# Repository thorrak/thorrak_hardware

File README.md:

# Thorrak's Hardware Designs
This repo is a collection of PCBs and other hardware designs I've made for various projects I've released. More information can be found on pages for each of the projects themselves.

**Note** - While the majority of the hardware for my projects is contained in this repo, the software is broken out into individual projects on GitHub. Most firmware can be flashed using [BrewFlasher](http://www.brewflasher.com/).

## BrewPi-ESP

The BrewPi-ESP project reimplements the BrewPi firmware on an ESP8266, ESP32, and ESP32-S2. 

- [Hardware Designs](BrewPi-ESP.md)
- [Project on GitHub](https://github.com/thorrak/brewpi-esp8266)

## TiltBridge

The TiltBridge project provides a Bluetooth-to-WiFi bridge for Tilt Hydrometers

- [Hardware/Container Designs](TiltBridge.md)
- [Project on GitHub](https://github.com/thorrak/tiltbridge/)

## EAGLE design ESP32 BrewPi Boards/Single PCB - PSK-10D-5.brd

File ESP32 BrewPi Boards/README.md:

# ESP32 BrewPi Controller Boards

# NOTE - This document is NOT complete/verified yet. 
## Please do not base a build on this doc without consulting Thorrak directly first!

Although the "heart" of a BrewPi controller is the microprocessor running the BrewPi-compatible firmware, without other
connected components that microcontroller cannot sense temperature, control power, or do any of the other things that
make a temperature controller useful. For the ESP32 version of this project, I have designed a single, "one size fits 
most" PCB that should work for virtually all builds -- as well as a handful of true "all-in-one" PCBs which integrate
the 5V 2A AC-to-DC power supply and 2-channel relay board that are typically required to be purchased/integrated
separately. 

| Board Design                                                                 | Tindie Order Link                                                                 | OSHPark Order Link                                    |
|------------------------------------------------------------------------------|-----------------------------------------------------------------------------------|-------------------------------------------------------|
| ["One Size Fits Most" D32 / D32 Pro](D32%20Pro%20-%20TFT%20OneSize.md)       | [Order](https://www.tindie.com/products/27251/)                                   | [Order](https://oshpark.com/shared_projects/iRLM23Fa) |
| ["All-in-One" D32 Pro PCB /w PSK-10D-5 PSU](Single%20PCB%20-%20PSK-10D-5.md) | [Order](https://www.tindie.com/products/thorrak/brewpi-esp32-all-in-one-pcb-kit/) | [Order](https://oshpark.com/shared_projects/oSOuiQbp) |
| ["All-in-One" D32 Pro PCB /w IRM-10-5 PSU](Single%20PCB%20-%20IRM-10-5.md)   | Coming Soon                                                                       | [Order]()                                             |

## "All-in-One" PCB Notes

The "All-in-One" PCBs are designed to eliminate much of the wiring, and many of the "common components" by combining the 
"main" PCB, 2-channel relay board, and DC power supply into a single, combined PCB. Due to supply constraints, there are
multiple designs, differing only by the power supply module they integrate. The PSK-10D-5 PSU is difficult to come by,
so most builders will want to choose the [IRM-10-5](Single%20PCB%20-%20IRM-10-5.md) version.

### Advantages to the "All-in-One" PCBs

- **Streamlined Assembly:** With fewer individual components, the build process is faster and less error-prone
- **Compact and Tidy Setup:** The all-in-one design results in a cleaner, more organized build
- **Reduced Wiring:** Single PCB design eliminates dupont cables and additional AC wiring

### Disadvantages to the "All-in-One" PCBs

- **Larger PCB Size:** The integrated design results in a larger PCB, which may increase fabrication costs at some manufacturers
- **Reduced Modularity:** If a component like the power supply or a relay fails, the entire board may need to be replaced or repaired
- **Power (Current) Limitations:** This board is not suitable for higher-amperage loads, which may limit its application in some setups

### Other Required Components

Like the "One Size Fits Most" PCB,  there are a handful of additional componets required for a complete, working build. 
This list is much smaller relative to other PCB types:

| Component                                                                | Qty |
|--------------------------------------------------------------------------|-----|
| [LOLIN D32 Pro](https://www.aliexpress.us/item/2251832696801305.html)    | 1   |
| [Ethernet cable](https://www.aliexpress.com/item/32694241950.html)       | 1   |
| [LOLIN TFT](https://www.aliexpress.us/item/2251832733414978.html)*       | 1   |
| [LOLIN TFT Cable](https://www.aliexpress.us/item/2251832662518722.html)* | 1   |

- There are many knock-off LOLIN boards sold by various sellers across the internet. Some of these may work, but purchasing directly from LOLIN is recommended.
- The ethernet cable is a standard, straight-through ethernet cable -- the same type as included with most home routers/networking equipment. If you have one already available, use it rather than ordering one.
- The LOLIN TFT & TFT Cable are only required if using the Lolin TFT display type. If using a separate, third-party TFT -- or not using a display at all -- these can be omitted

In addition to the above, this PCB is intended to be used in conjunction with a separate "Sensor Breakout Board" which
is then connected to this PCB via the RJ-45 (ethernet) cable listed above. To complete a full controller, you will need
the components listed on the [Sensor Board](../BrewPi%20Sensor%20Boards/README.md) pages as well.

## "One Size Fits Most" PCB Notes

This board supports the following features:
- Supports both [LoLin D32](https://www.wemos.cc/en/latest/d32/d32.html) and [LoLin D32 Pro](https://www.wemos.cc/en/latest/d32/d32_pro.html) controllers
- Supports both IIC and TFT screens
- Supports both the specific [LoLin D32 Pro screen](https://www.aliexpress.com/item/2251832733414978.html), as well as generic TFT screens
- Selectable OneWire voltage
- Optional TH-only configuration for easy assembly

### About Parts Links, Order Links, & Vendors

The BOM links provided are intended to serve as examples of the parts needed and are not the only place to source the 
parts listed.  Generally speaking, AliExpress is less expensive for parts.  The trade-off is that sometimes you are 
buying 100 at a time, and in most cases you are waiting for shipping.  DigiKey, Mouser, or other project part suppliers 
will probably have these parts as well and can generally ship much faster (albeit at much higher cost).

For convenience, order links are provided on each of the PCB's pages. Bare PCBs can be ordered from OshPark using the
link provided, or from your PCB-vendor-of-choice by uploading the Eagle design files (or converting them to gerbers
and uploading those). I also sometimes have PCBs available for sale on Tindie - including in some cases, either fully-
or partially-assembled boards. When you purchase through Tindie you are receiving a board or parts directly from me. 

#### TH Parts required to assemble the PCB

| Part                                                                                                                                       | Qty |
|--------------------------------------------------------------------------------------------------------------------------------------------|-----|
| [PCB](https://www.tindie.com/products/27251/)                                                                                              | 1   |
| [RJ45 Modular Jack w/no shield](https://www.digikey.com/en/products/detail/stewart-connector/SS-90000-001/14548964)                        | 1   |
| [2-terminal Screw Clamp](https://www.digikey.com/en/products/detail/w%C3%BCrth-elektronik/691137710002/6644051)                            | 1   |
| [4-Pin Male Pin Header](https://www.digikey.com/en/products/detail/sullins-connector-solutions/PRPC040SAAN-RC/2775214)                     | 2   |
| [3-Pin Male Pin Header](https://www.digikey.com/en/products/detail/sullins-connector-solutions/PRPC040SAAN-RC/2775214)                     | 1   |
| [2-Pin Male Pin Header](https://www.digikey.com/en/products/detail/sullins-connector-solutions/PRPC040SAAN-RC/2775214)                     | 1   |
| [16-Pin Female Pin Header](https://www.digikey.com/en/products/detail/sullins-connector-solutions/PPTC161LFBN-RC/810154)                   | 2   |
| [10-Pin (2x5) Box Header](https://www.digikey.com/en/products/detail/amphenol-cs-commercial-products/G821EU210AGM00Y/13683147) (Optional*) | 1   |
| [2.54mm Jumper](https://www.digikey.com/en/products/detail/sullins-connector-solutions/STC02SYAN/76372)**                                  | 1   |

*- The 10-pin box header is optional, but enables the use of a non-Lolin TFT screen attached to an LCD breakout PCB. If using an IIC screen or the [LoLin D32 Pro screen](https://www.aliexpress.com/item/2251832733414978.html) + [cable](https://www.aliexpress.com/item/2251832662518722.html), this can be left off.
**- The 2.54mm jumper is probably included on the 2-channel relay board you will purchase as part of the "common component" set below

### SMD Components required to assemble the PCB

Note - You will not need the following if you purchased the partially-assembled PCB from my [Tindie store](https://www.tindie.com/products/27251/). 

This board supports assembly with both SMD and TH components -- you can choose between the SMD components linked below 
and the TH components in the second table. You will not need both. The SMD components will enable the LCD2004 screen 
option - this screen will not work if you use the TH component set. 

| SMD Parts                                                                                                                     | Qty |
|-------------------------------------------------------------------------------------------------------------------------------|-----|
| [10k 0805 Resistor](https://www.digikey.com/en/products/detail/stackpole-electronics-inc/RNCP0805FTD10K0/2240262)             | 4   |
| [4.7k 0805 Resistor](https://www.digikey.com/en/products/detail/te-connectivity-passive-product/CRGCQ0805J4K7/8576740)        | 1   |
| [0.1uF (100nF) 0805 Capacitor](https://www.digikey.com/en/products/detail/samsung-electro-mechanics/CL21B104KACNNNC/3886757)  | 2   |
| [1.0uF 0805 Capacitor](https://www.digikey.com/en/products/detail/samsung-electro-mechanics/CL21B105KAFNNNE/3886724)          | 2   |
| [BSS138 MOSFET](https://www.digikey.com/en/products/detail/onsemi/BSS138/244210)                                              | 2   |

This is the optional, alternative TH part set. You **DO NOT** need these parts if you ordered either the SMD parts above, or the partially-assembled PCB:

| Alternative TH Part                                                                                      | Qty |
|----------------------------------------------------------------------------------------------------------|-----|
| [4.7k Resistor](https://www.digikey.com/en/products/detail/stackpole-electronics-inc/CF14JT4K70/1741428) | 1   |
| [0.1uF (100nF) Capacitor](https://www.digikey.com/en/products/detail/kemet/C315C104M5U5TA/817927)        | 2   |
| [1.0uF Capacitor](https://www.digikey.com/en/products/detail/kemet/C320C105K5N5TA7301/12701373)          | 2   |

### Other Required Components

Below are the other "required" components for almost every build: 

| Component                                                                            | Qty |
|--------------------------------------------------------------------------------------|-----|
| [LOLIN D32 Pro](https://www.aliexpress.com/item/2251832696801305.html)               | 1   |
| [2-Channel 5V Relay Board](https://www.aliexpress.com/item/32997387727.html)         | 1   |
| [Ethernet cable](https://www.aliexpress.com/item/32694241950.html)                   | 1   |
| [5V 2A Power Supply Module](https://www.aliexpress.com/item/32900418425.html)        | 1   |
| [Dupont Cables (Female-to-Female)](https://www.aliexpress.com/item/33039596089.html) | 13* |

In addition to the above, this PCB is intended to be used in conjunction with a separate "Sensor Breakout Board" which 
is then connected to this PCB via the RJ-45 (ethernet) cable listed above. To complete a full controller, you will need
the components listed on the [Sensor Board](../BrewPi%20Sensor%20Boards/README.md) pages as well.

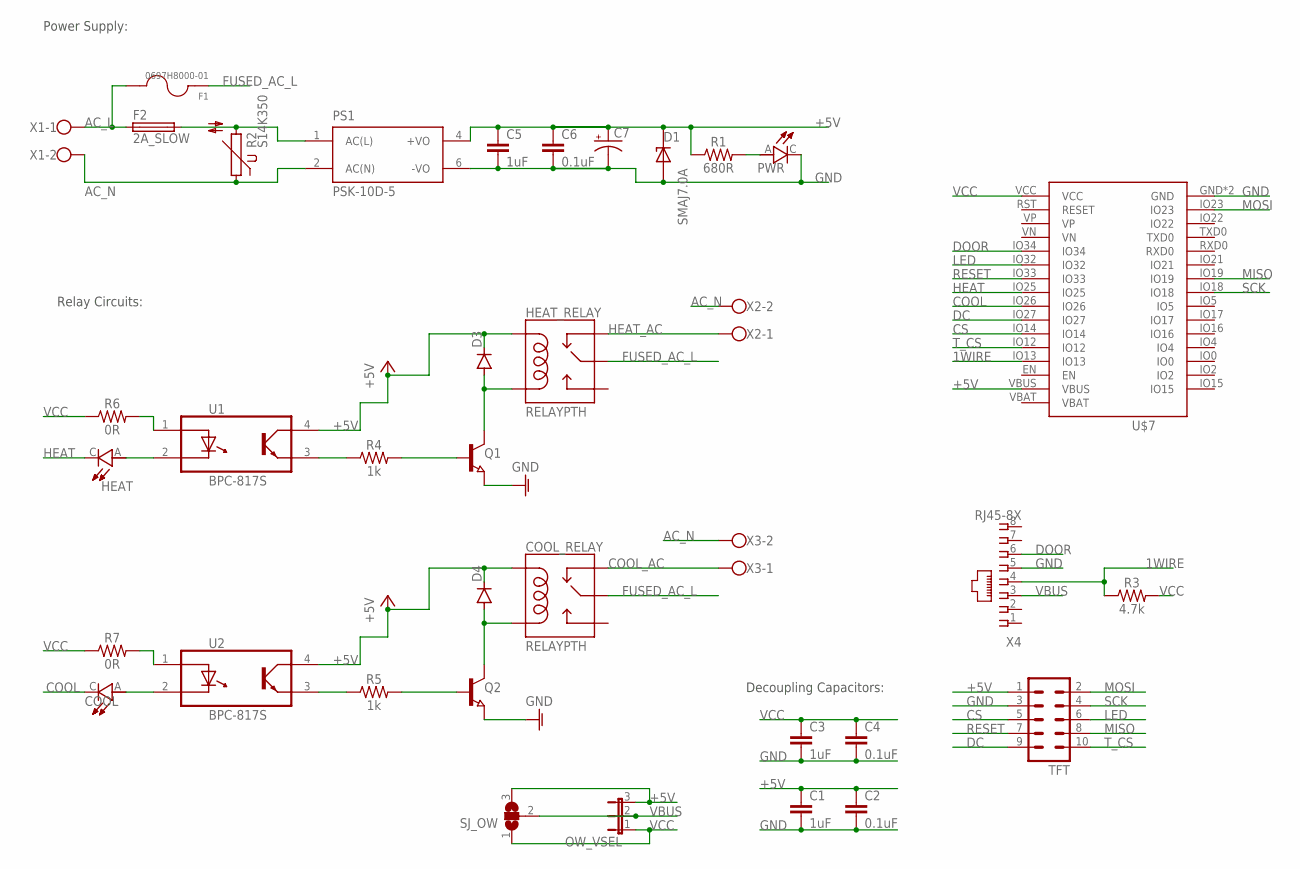
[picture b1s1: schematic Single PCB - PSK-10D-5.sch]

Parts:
C1, C3, C5: 1uF; SMD-0805; LCSC_PART C28323
C2, C4, C6: 0.1uF; SMD-0805; LCSC_PART C49678
C7: 220uF; CAPPRD750W80D1600H2700; LCSC_PART C43349
COOL: LED_0603LED_SMD_0603; LED_SMD_0603; LCSC_PART C2286
COOL_RELAY: RELAYPTH; SRD-05VDC-SL-C
D1: SMAJ7.0A; DIOM4325X250N; LCSC_PART C309904
D3, D4: DIODE-DO214AC; DO214AC; LCSC_PART C95872
F1: 0697H8000-01; FUSRR508W60L835T400H810
F2: 2A_SLOW; FUSE_BK/PCE-5-R; DIGIKEY 283-4166-1-ND
HEAT: LED_0603LED_SMD_0603; LED_SMD_0603; LCSC_PART C2286
HEAT_RELAY: RELAYPTH; SRD-05VDC-SL-C
OW_VSEL: JP2ENOLABEL; JP2-NOLABEL
PS1: PSK-10D-5; CONV_PSK-10D-5
PWR: LED_0603LED_SMD_0603; LED_SMD_0603; LCSC_PART C2286
Q1, Q2: NPN-TRANSISTOR_SOT23; SOT23
R1: 680R; SMD-0805; LCSC_PART C17798
R2: S14K350; S10K350; LCSC_PART C78355
R3: 4.7k; SMD-0805; LCSC_PART C17673
R4, R5: 1k; SMD-0805; LCSC_PART C17513
R6, R7: 0R; SMD-0805; LCSC_PART C17477
SJ_OW: SJ2W; SJ_2
TFT: MA05-2
U1, U2: BPC-817S; SOIC127P700X210-4N
U$7: WEMOS-D32D32_PRO_NO-KEEPOUT; D32_PRO_NO-KEEPOUT
X1, X2, X3: W237-102
X4: RJ45-8X; RJ45-NO-SHIELD

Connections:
1WIRE: R3.1, U$7.IO13, X4.4
+5V: C1.1, C2.1, C5.1, C6.1, C7.2 (+), COOL_RELAY.COIL1, D1.C, D3.C, D4.C, HEAT_RELAY.COIL1, OW_VSEL.3, PS1.4 (+VO), R1.1, SJ_OW.3, TFT.1, U1.4 (CO), U2.4 (CO), U$7.VBUS
AC_L: F1.2, F2.1, X1.1
AC_N: PS1.2 (AC(N)), R2.1, X1.2, X2.2, X3.2
COOL: COOL.C, U$7.IO26
COOL_AC: COOL_RELAY.SWCLOSED (SWCLOSE), X3.1
CS: TFT.5, U$7.IO14
DC: TFT.9, U$7.IO27
DOOR: U$7.IO34, X4.6
FUSED_AC_L: COOL_RELAY.SWCOMMON, F1.1, HEAT_RELAY.SWCOMMON
GND: C1.2, C2.2, C3.2, C4.2, C5.2, C6.2, C7.1 (-), D1.A, PS1.6 (-VO), PWR.C, Q1.2 (E), Q2.2 (E), TFT.3, U$7.GND, U$7.GND2 (GND), X4.5
HEAT: HEAT.C, U$7.IO25
HEAT_AC: HEAT_RELAY.SWCLOSED (SWCLOSE), X2.1
LED: TFT.6, U$7.IO32
MISO: TFT.8, U$7.IO19
MOSI: TFT.2, U$7.IO23
unnamed: Q1.1 (B), R4.2
unnamed: F2.2, PS1.1 (AC(L)), R2.2
unnamed: PWR.A, R1.2
unnamed: R4.1, U1.3 (E)
unnamed: COOL_RELAY.COIL0, D4.A, Q2.3 (C)
unnamed: R5.1, U2.3 (E)
unnamed: Q2.1 (B), R5.2
unnamed: R6.2, U1.1 (A)
unnamed: R7.2, U2.1 (A)
unnamed: HEAT.A, U1.2 (C)
unnamed: D3.A, HEAT_RELAY.COIL0, Q1.3 (C)
unnamed: COOL.A, U2.2 (C)
RESET: TFT.7, U$7.IO33
SCK: TFT.4, U$7.IO18
T_CS: TFT.10, U$7.IO12
VBUS: OW_VSEL.2, SJ_OW.2, X4.3
VCC: C3.1, C4.1, OW_VSEL.1, R3.2, R6.1, R7.1, SJ_OW.1, U$7.VCC

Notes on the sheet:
Power Supply:
Relay Circuits:
Decoupling Capacitors:

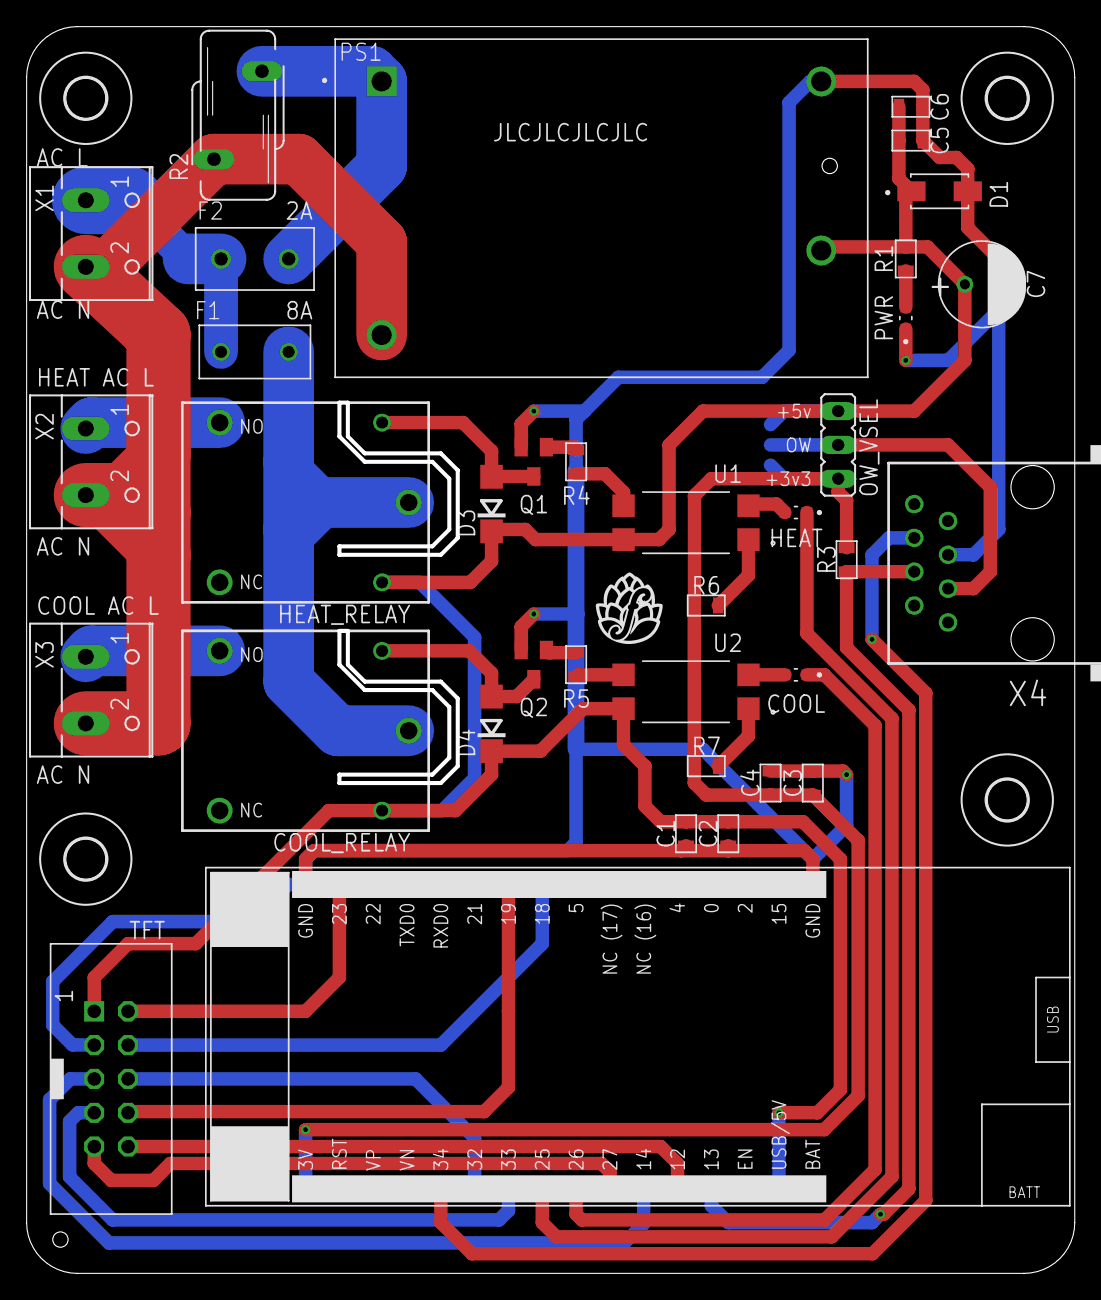
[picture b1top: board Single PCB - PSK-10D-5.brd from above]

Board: 2 copper layers, 78.7 x 93.7 mm, 43 parts (1 on the bottom side), 33 nets.

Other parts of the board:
U$1, U$2, U$3, U$4: 3,0
U$5, U$6: 1.152

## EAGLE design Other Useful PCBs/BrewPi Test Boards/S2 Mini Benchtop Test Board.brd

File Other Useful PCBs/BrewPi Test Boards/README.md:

# BrewPi-ESP Test Boards

These PCBs were designed specifically to help test new firmware revisions of BrewPi-ESP on different hardware. There are multiple designs, enabling testing on different controllers and screen configurations.

- [D32/D32 Pro Benchtop Test Board](D32%20Pro%20Benchtop%20Test%20Board.md)
- [D1 Mini/S2 Mini Benchtop Test Board](S2%20Mini%20Benchtop%20Test%20Board.md)

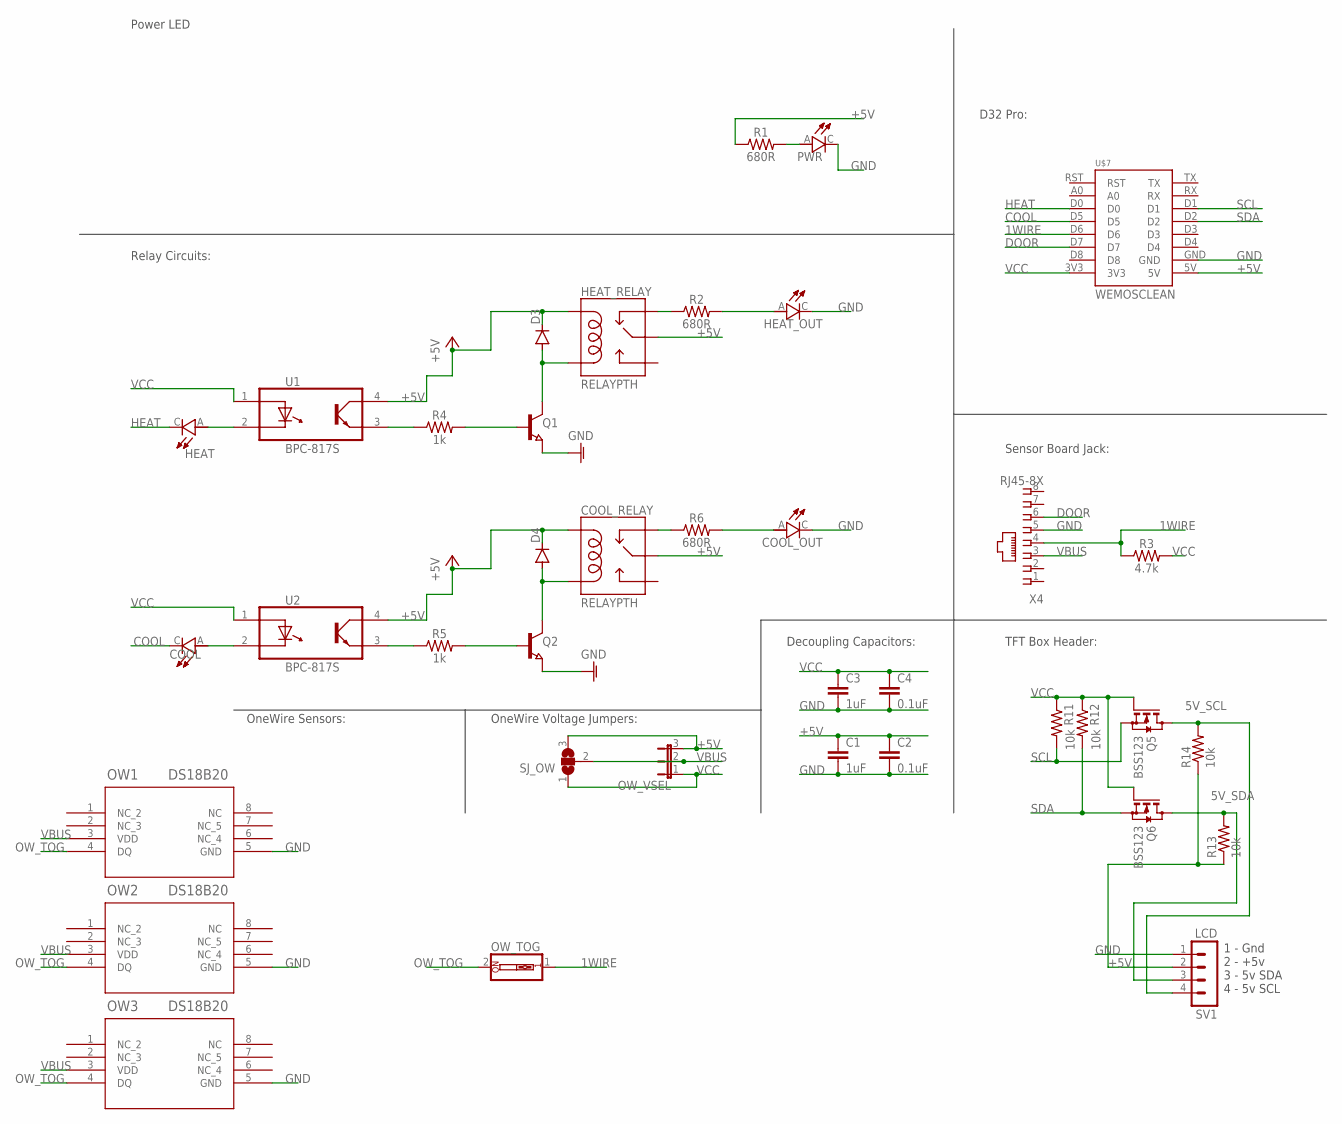
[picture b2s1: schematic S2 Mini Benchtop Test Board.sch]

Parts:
C1, C3: 1uF; SMD-0805; LCSC_PART C28323
C2, C4: 0.1uF; SMD-0805; LCSC_PART C49678
COOL: LED_0603LED_SMD_0603; LED_SMD_0603; LCSC_PART C2286
COOL_OUT: LED_0603LED_SMD_0603; LED_SMD_0603
COOL_RELAY: RELAYPTH; SRD-05VDC-SL-C
D3, D4: DIODE-DO214AC; DO214AC; LCSC_PART C95872
HEAT: LED_0603LED_SMD_0603; LED_SMD_0603; LCSC_PART C2286
HEAT_OUT: LED_0603LED_SMD_0603; LED_SMD_0603
HEAT_RELAY: RELAYPTH; SRD-05VDC-SL-C
OW1, OW2, OW3: DS18B20; 21-0041B_8_MXM
OW_TOG: SW_DIP-1; EDG-01; LCSC_PART C126888
OW_VSEL: JP2ENOLABEL; JP2-NOLABEL; LCSC_PART C2937625
PWR: LED_0603LED_SMD_0603; LED_SMD_0603; LCSC_PART C2286
Q1, Q2: NPN-TRANSISTOR_SOT23; SOT23; JLC_R -90
Q5, Q6: BSS123; SOT23; JLC_R -90
R1, R2, R6: 680R; SMD-0805; LCSC_PART C17798
R3: 4.7k; SMD-0805; LCSC_PART C17673
R4, R5: 1k; SMD-0805; LCSC_PART C17513
R11, R12, R13, R14: 10k; R0805; LCSC_PART C17902
SJ_OW: SJ2W; SJ_2
SV1: LCD; HDR-4_VERT; LCSC_PART C2691448
U1, U2: BPC-817S; SOIC127P700X210-4N
U$7: WEMOSCLEAN; WEMOS-CLEAN
X4: RJ45-8X; RJ45-NO-SHIELD; JLC_Y 7.55

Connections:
1WIRE: OW_TOG.1, R3.1, U$7.D6, X4.4
5V_SCL: Q5.3 (D), R14.2, SV1.4
5V_SDA: Q6.3 (D), R13.2, SV1.3
+5V: C1.1, C2.1, COOL_RELAY.COIL1, COOL_RELAY.SWCOMMON, D3.C, D4.C, HEAT_RELAY.COIL1, HEAT_RELAY.SWCOMMON, OW_VSEL.3, R1.1, R13.1, R14.1, SJ_OW.3, SV1.2, U1.4 (CO), U2.4 (CO), U$7.5V
COOL: COOL.C, U$7.D5
DOOR: U$7.D7, X4.6
GND: C1.2, C2.2, C3.2, C4.2, COOL_OUT.C, HEAT_OUT.C, OW1.5 (GND), OW2.5 (GND), OW3.5 (GND), PWR.C, Q1.2 (E), Q2.2 (E), SV1.1, U$7.GND, X4.5
HEAT: HEAT.C, U$7.D0
unnamed: Q1.1 (B), R4.2
unnamed: PWR.A, R1.2
unnamed: R4.1, U1.3 (E)
unnamed: COOL_RELAY.COIL0, D4.A, Q2.3 (C)
unnamed: R5.1, U2.3 (E)
unnamed: Q2.1 (B), R5.2
unnamed: COOL_RELAY.SWCLOSED (SWCLOSE), R6.1
unnamed: COOL_OUT.A, R6.2
unnamed: HEAT_OUT.A, R2.2
unnamed: HEAT_RELAY.SWCLOSED (SWCLOSE), R2.1
unnamed: HEAT.A, U1.2 (C)
unnamed: D3.A, HEAT_RELAY.COIL0, Q1.3 (C)
unnamed: COOL.A, U2.2 (C)
OW_TOG: OW1.4 (DQ), OW2.4 (DQ), OW3.4 (DQ), OW_TOG.2
SCL: Q5.2 (S), R11.2, U$7.D1
SDA: Q6.2 (S), R12.2, U$7.D2
VBUS: OW1.3 (VDD), OW2.3 (VDD), OW3.3 (VDD), OW_VSEL.2, SJ_OW.2, X4.3
VCC: C3.1, C4.1, OW_VSEL.1, Q5.1 (G), Q6.1 (G), R3.2, R11.1, R12.1, SJ_OW.1, U1.1 (A), U2.1 (A), U$7.3V3

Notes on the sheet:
Power LED
Relay Circuits:
Decoupling Capacitors:
TFT Box Header:
Sensor Board Jack:
OneWire Voltage Jumpers:
OneWire Sensors:
D32 Pro:
1 - Gnd 2 - +5v 3 - 5v SDA 4 - 5v SCL

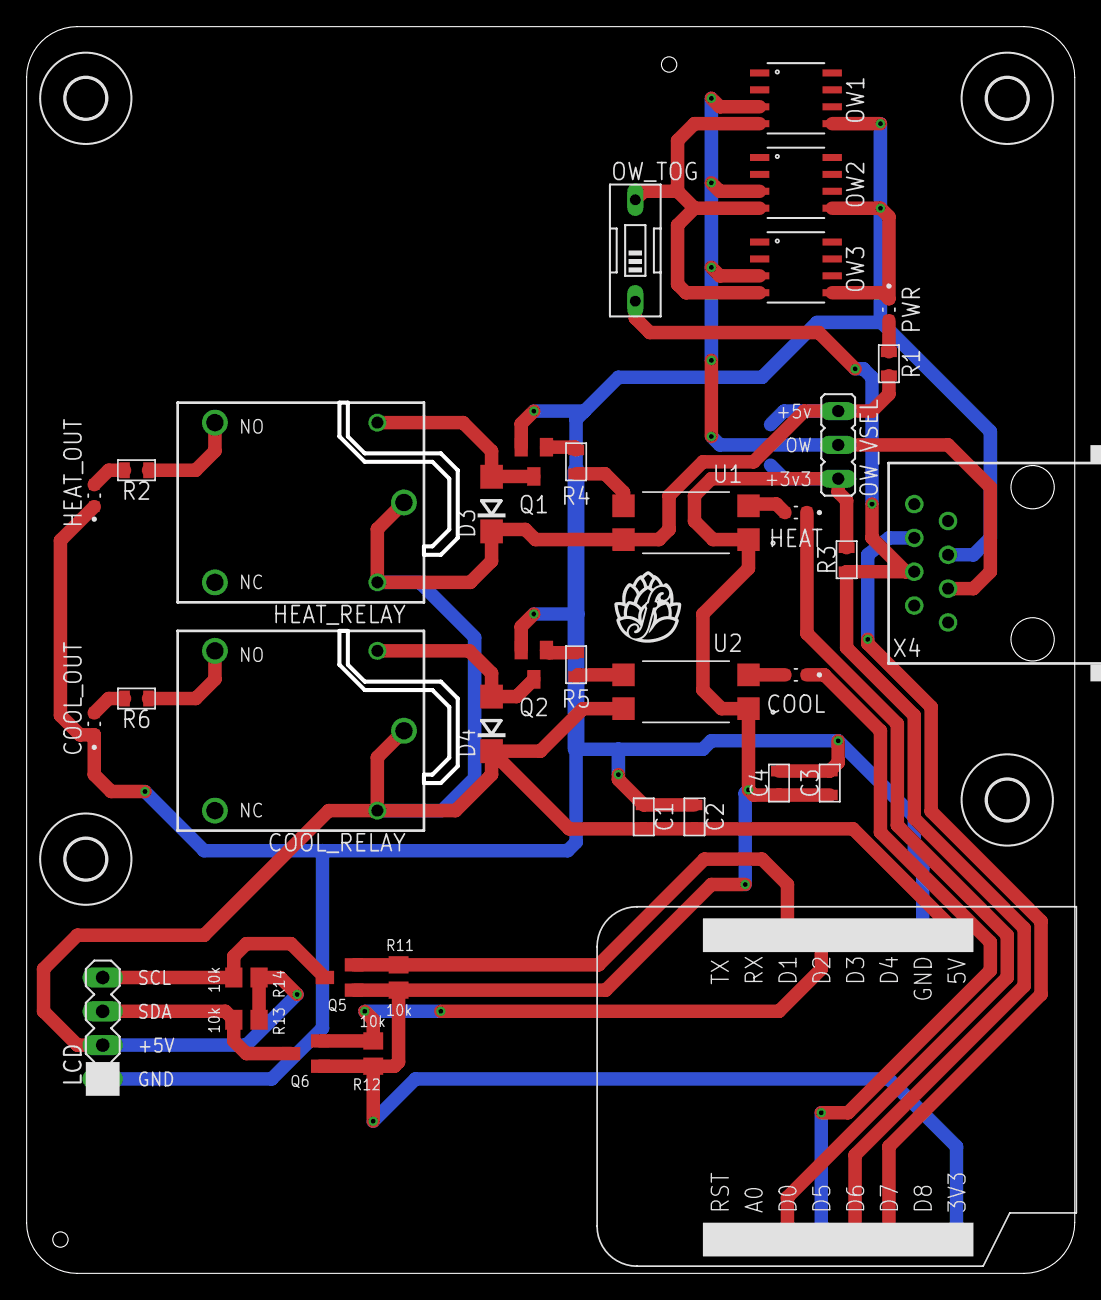
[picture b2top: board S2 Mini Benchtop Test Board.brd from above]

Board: 2 copper layers, 78.7 x 93.7 mm, 44 parts (1 on the bottom side), 26 nets.

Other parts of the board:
U$1, U$2, U$3, U$4: 3,0
U$5, U$6: 1.152

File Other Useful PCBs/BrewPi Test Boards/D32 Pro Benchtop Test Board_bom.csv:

Comment,Designator,Footprint,LCSC Part #
1uF,C1 C3,SMD-0805,C28323
0.1uF,C2 C4,SMD-0805,C49678
LED_0603LED_SMD_0603,COOL COOL_OUT HEAT HEAT_OUT PWR,LED_SMD_0603,C2286
RELAYPTH,COOL_RELAY HEAT_RELAY,SRD-05VDC-SL-C,C35449
,D3 D4,DO214AC,C95872
,DOOR_SW OW_TOG,EDG-01,C126888
DS18B20,OW1 OW2 OW3,21-0041B_8_MXM,C695837
,OW_VSEL,JP2-NOLABEL,C2937625
,Q1 Q2,SOT23,C20526
BSS123,Q5 Q6,SOT23,C79015
680R,R1 R2 R6,SMD-0805,C17798
4.7k,R3,SMD-0805,C17673
1k,R4 R5,SMD-0805,C17513
10k,R11 R12 R13 R14,R0805,C17902
LCD,SV1,HDR-4_VERT,C2691448
WEMOS-D32D32_PRO_NO-KEEPOUT,U$7 U$8,D32_PRO_NO-KEEPOUT,C18078137
BPC-817S,U1 U2,SOIC127P700X210-4N,C106900
RJ45-8X,X4,RJ45-NO-SHIELD,C3000197

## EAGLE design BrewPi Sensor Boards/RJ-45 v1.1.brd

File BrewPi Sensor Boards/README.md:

BrewPi Sensor Boards
====================

The BrewPi sensor boards are intended to allow the DS18b20 temperature sensors (and optionally, door switch) to be connected to a PCB that is away from your main BrewPi controller, thereby allowing for the use of shorter temperature sensor cables - or for the placement of the sensor breakout inside your fermentation chamber if necessary. The sensor boards are then intended to be connected to the main controller board through the use of a cable.

All the up-to-date "main" controller board designs use RJ-45 jacks and are intended to be paired with the RJ-45 Breakout Board:

| Design                                               | Order                                                 | Buy on Tindie                                                                                 | Jack Type |
| ---------------------------------------------------- | ----------------------------------------------------- |-----------------------------------------------------------------------------------------------| --------- |
| [RJ-45 Breakout Board](RJ-45%20Sensor%20Breakout.md) | [Order](https://oshpark.com/shared_projects/5gqoDyRn) | [Buy](https://www.tindie.com/products/thorrak/brewpi-esp-rj45-sensor-breakout-board-v11-pcb/) | RJ-45     |

## Legacy Breakout Board Designs

Older versions of the "main" controller board designs used RJ-11 jacks and were intended to be connected via telephone cables. Unfortunately, telephone cables are frequently found in both the "straight through" and "crossover" versions, and as a result many builds failed as a result of using the wrong cable type.

**New builds should use the RJ-45 boards.** Users with older controller PCBs that need the RJ-11 breakout board design can find it in the ["legacy"](legacy/RJ-11%20Sensor%20Breakout.md) folder in this repo.

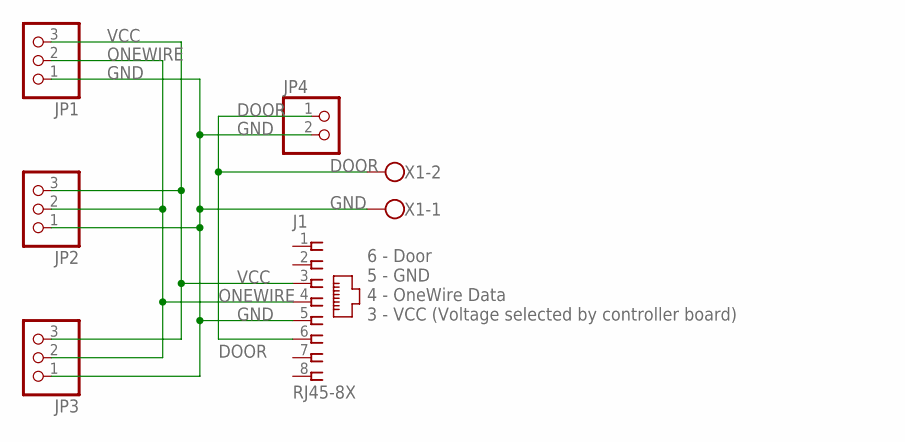
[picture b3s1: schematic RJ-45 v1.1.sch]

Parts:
J1: RJ45-8X; RJ45-NS-XDIM
JP1, JP2, JP3: PINHD-1X3; 1X03
JP4: PINHD-1X2; 1X02
X1: W237-102

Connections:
DOOR: J1.6, JP4.1, X1.2
GND: J1.5, JP1.1, JP2.1, JP3.1, JP4.2, X1.1
ONEWIRE: J1.4, JP1.2, JP2.2, JP3.2
VCC: J1.3, JP1.3, JP2.3, JP3.3

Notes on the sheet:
6 - Door 5 - GND 4 - OneWire Data 3 - VCC (Voltage selected by controller board)

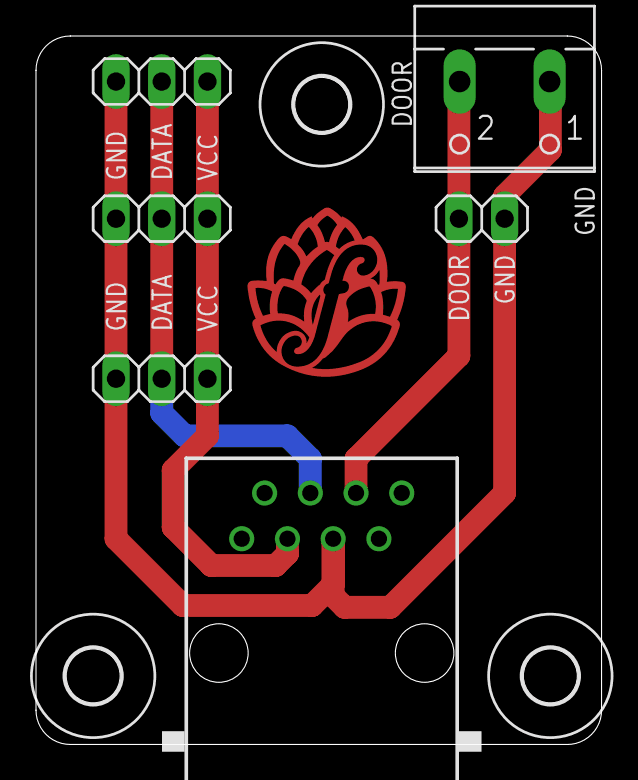
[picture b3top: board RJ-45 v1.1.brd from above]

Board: 2 copper layers, 31.4 x 39.4 mm, 9 parts (0 on the bottom side), 4 nets.

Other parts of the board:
U$1, U$2, U$3: 3,0

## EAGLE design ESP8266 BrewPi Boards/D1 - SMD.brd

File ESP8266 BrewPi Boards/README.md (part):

ESP8266 BrewPi Controller Boards
================================

Although the "heart" of a BrewPi controller is the microprocessor running the BrewPi-compatible firmware, without other connected components that microcontroller cannot sense temperature, control power, or do any of the other things that make a temperature controller useful. Several PCBs have been designed to help simplify the wiring of the microcontroller to those other components.

Six different versions of the main "controller" PCB are listed here.  Each provide different functionality and/or form factors:

*   No LCD Support with DuPont connectors and through-hole components
*   LCD Support with DuPont connectors and surface-mount level converter components
*   LCD Support with DuPont connectors, through-hole components, and a SparkFun-based level converter sub-board
*   LCD Support with screw connectors, through-hole components, and a SparkFun-based level converter sub-board
*   LCD Support with DuPont connectors, through-hole components, and an integrated level converter
*   LCD Support with DuPont connectors, through-hole components, a SparkFun-based level converter sub-board, and direct connections for temperature sensors

| Board Design                                                                                                             | Order Link                                             | Through Hole        | Surface Mount       | I2C LCD             | Connector Type   | Integrated Level Shifter  | Selectable OneWire Voltage  |
|--------------------------------------------------------------------------------------------------------------------------|--------------------------------------------------------|---------------------|---------------------|---------------------|------------------|---------------------------|-----------------------------|
| [Surface Mount](D1%20-%20SMD.md)                                                                                         | [Order](https://oshpark.com/shared_projects/1slCGU7M)  |                     | :heavy_check_mark:  | :heavy_check_mark:  | Dupont           | :heavy_check_mark:        | :heavy_check_mark:          |
| [TH - Sparkfun /w Dupont Cables](D1%20-%20LCD%20TH%20Dupont.md)                                                          | [Order](https://oshpark.com/shared_projects/ZyUfectQ)  | :heavy_check_mark:  |                     | :heavy_check_mark:  | Dupont           |                           | :heavy_check_mark:          |
| [TH - MOSFETs](https://github.com/brewpi-remix/brewpi-pcb-rmx/tree/master/ESP8266%20Boards/WeMos%20D1%20Mini%20Breakout) | [Order](https://oshpark.com/shared_projects/YLXZEzde)  | :heavy_check_mark:  |                     | :heavy_check_mark:  | Dupont           | :heavy_check_mark:        |                             |
| [TH - Sparkfun /w Screw Terminals](D1%20-%20LCD%20TH%20Screws.md)                                                        | [Order](https://oshpark.com/shared_projects/OmKNGkVm)  | :heavy_check_mark:  |                     | :heavy_check_mark:  | Screw Terminals  |                           | :heavy_check_mark:          |
| [TH - No LCD](D1%20-%20No%20LCD.md)                                                                                      | [Order](https://oshpark.com/shared_projects/TOON0jUw)  | :heavy_check_mark:  |                     |                     | Dupont           |                           | :heavy_check_mark:          |
| [TH - Sparkfun /w Dupont Cables NoRJ](D1%20-%20LCD%20TH%20Dupont%20NoRJ.md)                                              | [Order](https://oshpark.com/shared_projects/hdqCEBHe)  | :heavy_check_mark:  |                     | :heavy_check_mark:  | Dupont           |                           | :heavy_check_mark:          |

### About Parts Links, Order Links, & Vendors

The BOM links provided are intended to serve as examples of the parts needed and are not the only place to source the parts listed.  Generally speaking, AliExpress is less expensive for parts.  The trade-off is that sometimes you are buying 100 at a time, and in most cases you are waiting for shipping.  DigiKey, Mouser, or other project part suppliers will probably have these parts as well and can generally ship much faster (albeit at much higher cost).

For convenience, order links are provided on each of the PCB's pages to a handful of PCB vendors. OshPark tends to be one of the more expensive board aggregators, but also happens to be one of the faster/more reliable ones. DirtyPCBs tends to be cheaper (especially when ordering in bulk) but ship from China and can take awhile to arrive. When I have PCBs either available or left over, I sometimes offer them for sale on Tindie - when you purchase through Tindie you are receiving a board or parts directly from me. 

The direct links to DirtyPCBs include a small premium (10%) which is credited into my DirtyPCBs account. That credit is used in the development of these and other projects. Anyone who has done development like this can tell you how many boards we go through, and the cost is not insignificant. If you prefer to avoid this markup you may absolutely take these files from GitHub and upload them yourself. In the spirit of transparency, If you do purchase through these links it's only fair I tell you about it and what I will do with the credits.

Features Explained
------------------

### Through Hole vs. Surface Mount

Through Hole components generally have a wire or pin that goes through a hole on the PCB, enabling easy soldering on the back-side of the circuit board. By contrast, Surface Mount components are attached directly to the surface of a PCB with small dots of solder. The overwhelming majority of PCBs use primarily surface mount components - but as these are more difficult to solder by hand, many hobbyists prefer hand-soldering through hole components. 

Choose "surface mount" if you want a compact board and are comfortable learning to solder surface mount components. Choose "through hole" if you are not comfortable soldering and would prefer the easiest option.

### I2C LCD

The ESP8266 port of the BrewPi firmware supports the utilization of an LCD screen connected via an "I2C" interface. Due to the nature of these LCD screens this requires additional hardware which increases the size & complexity of the board - but the slight amount of additional pain when building the controller pays off in the increased utility of having an LCD.

Choose this option if you want an LCD screen. Ignore this option if you prefer the cheapest board available (and are OK with not having an LCD).

### Connector Type - Dupont vs. Screw Terminals

"Dupont" cables are a type of cable that has a single female header at each end. This allows for connecting two devices with "pin header" interfaces through the use of a compact "ribbon"-type cable. 

Boards that are "dupont" style have compact pin-headers on them, and can only be used with Dupont cables. By contrast, "screw terminal" style boards are designed to have screw terminals soldered on which makes attaching/detaching cables easier. Screw-terminal boards are larger but can be optionally used with pin headers as well, however "dupont" style boards are not compatible with screw terminals.

Choose "dupont" if you want a cheaper, smaller board. Choose "screw terminals" if you prefer much larger soldering pads. 

### Integrated Level Shifter

I2C LCDs require that the 3.3 volt logic from the ESP8266 be "translated" to the 5 volt logic required by the LCD. This is done through the use of a "level shifter". Level shifters are relatively simple components, but require soldering a number of things by hand which some hobbyists would prefer not to do. The boards with integrated level shifters have these additional components as part of the PCB, while those boards without an integrated level shifter use a "sparkfun"-style level shifter which is attached to the board using pin headers. 

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
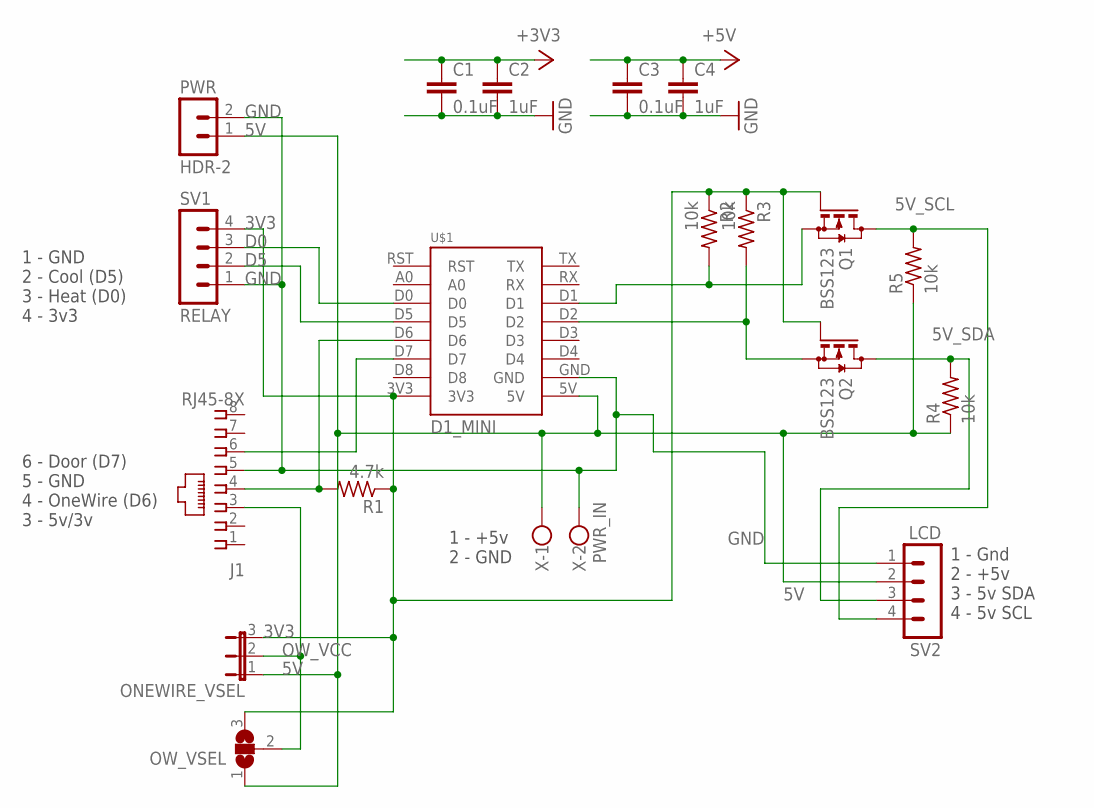
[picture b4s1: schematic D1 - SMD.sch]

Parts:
C1, C3: 0.1uF; C0805
C2, C4: 1uF; C0805
J1: RJ45-8X; RJ45-NO-SHIELD-NOLINE
ONEWIRE_VSEL: JP2ENOLABEL; JP2-NOLABEL
OW_VSEL: SJ2W; SJ_2
PWR: HDR-2; HDR-2_VERT
Q1, Q2: BSS123; SOT23
R1: 4.7k; R0805
R2, R3, R4, R5: 10k; R0805
SV1: RELAY; HDR-4_VERT
SV2: LCD; HDR-4_VERT
U$1: D1_MINI; WEMOS-CLEAN
X: PWR_IN; W237-102

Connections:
3V3: C1.1, C2.1, ONEWIRE_VSEL.3, OW_VSEL.3, Q1.1 (G), Q2.1 (G), R1.1, R2.1, R3.1, SV1.4, U$1.3V3
3V3_SCL: Q1.2 (S), R2.2, U$1.D1
3V3_SDA: Q2.2 (S), R3.2, U$1.D2
5V: C3.1, C4.1, ONEWIRE_VSEL.1, OW_VSEL.1, PWR.1, R4.1, R5.1, SV2.2, U$1.5V, X.1
5V_SCL: Q1.3 (D), R5.2, SV2.4
5V_SDA: Q2.3 (D), R4.2, SV2.3
D0: SV1.3, U$1.D0
D5: SV1.2, U$1.D5
D6: J1.4, R1.2, U$1.D6
D7: J1.6, U$1.D7
GND: C1.2, C2.2, C3.2, C4.2, J1.5, PWR.2, SV1.1, SV2.1, U$1.GND, X.2
OW_VCC: J1.3, ONEWIRE_VSEL.2, OW_VSEL.2

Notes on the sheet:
1 - GND 2 - Cool (D5) 3 - Heat (D0) 4 - 3v3
6 - Door (D7) 5 - GND 4 - OneWire (D6) 3 - 5v/3v
1 - +5v 2 - GND
1 - Gnd 2 - +5v 3 - 5v SDA 4 - 5v SCL

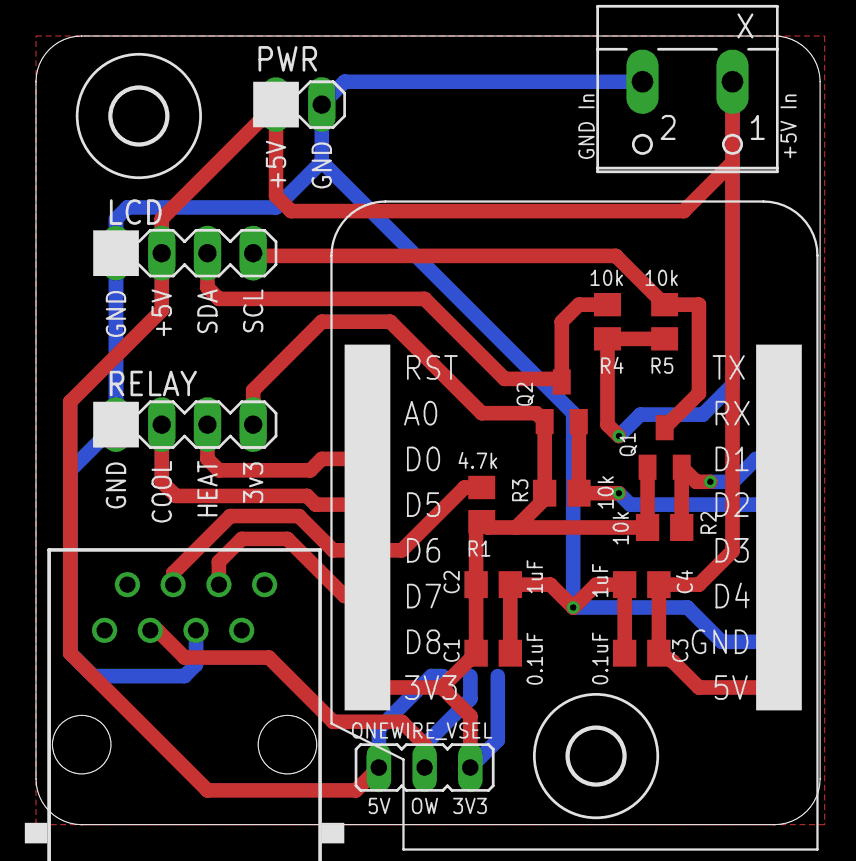
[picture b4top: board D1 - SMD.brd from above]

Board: 2 copper layers, 43.6 x 43.8 mm, 21 parts (1 on the bottom side), 12 nets.

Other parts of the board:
U$2, U$4: 3,0

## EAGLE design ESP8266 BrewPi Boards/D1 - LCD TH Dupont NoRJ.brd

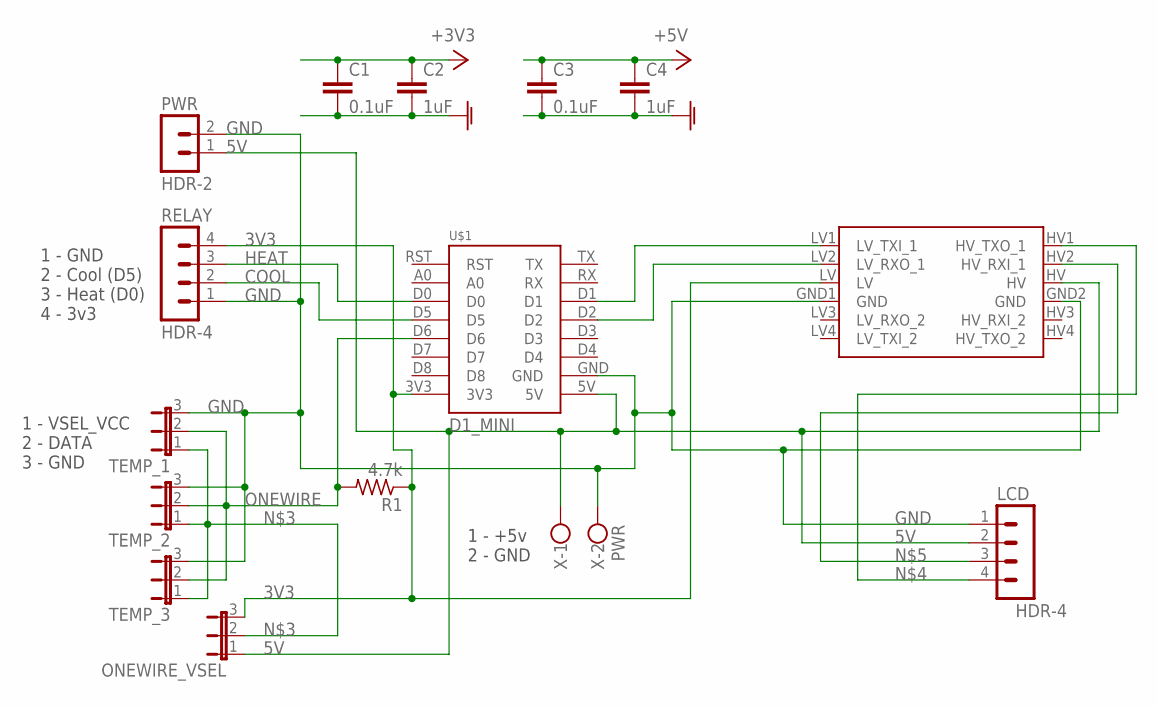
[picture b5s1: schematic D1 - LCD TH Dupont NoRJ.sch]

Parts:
C1, C3: 0.1uF; C050-035X075
C2, C4: 1uF; C050-035X075
LCD: HDR-4; HDR-4_VERT
ONEWIRE_VSEL: JP2ENOLABEL; JP2-NOLABEL
PWR: HDR-2; HDR-2_VERT
R1: 4.7k; 0309/12
RELAY: HDR-4; HDR-4_VERT
TEMP_1, TEMP_2, TEMP_3: JP2ENOLABEL; JP2-NOLABEL
U$1: D1_MINI; WEMOS-CLEAN
U$3: SPARKFUN_LOGIC_LEVEL_CONVERTER
X: PWR; W237-102

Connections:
3V3: C1.1, C2.1, ONEWIRE_VSEL.3, R1.1, RELAY.4, U$1.3V3, U$3.LV
5V: C3.1, C4.1, LCD.2, ONEWIRE_VSEL.1, PWR.1, U$1.5V, U$3.HV, X.1
COOL: RELAY.2, U$1.D5
GND: C1.2, C2.2, C3.2, C4.2, LCD.1, PWR.2, RELAY.1, TEMP_1.3, TEMP_2.3, TEMP_3.3, U$1.GND, U$3.GND1 (GND), U$3.GND2 (GND), X.2
HEAT: RELAY.3, U$1.D0
unnamed: U$1.D1, U$3.LV1 (LV_TXI_1)
unnamed: U$1.D2, U$3.LV2 (LV_RXO_1)
unnamed: ONEWIRE_VSEL.2, TEMP_1.1, TEMP_2.1, TEMP_3.1
unnamed: LCD.4, U$3.HV1 (HV_TXO_1)
unnamed: LCD.3, U$3.HV2 (HV_RXI_1)
ONEWIRE: R1.2, TEMP_1.2, TEMP_2.2, TEMP_3.2, U$1.D6

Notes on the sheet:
1 - GND 2 - Cool (D5) 3 - Heat (D0) 4 - 3v3
1 - +5v 2 - GND
1 - VSEL_VCC 2 - DATA 3 - GND

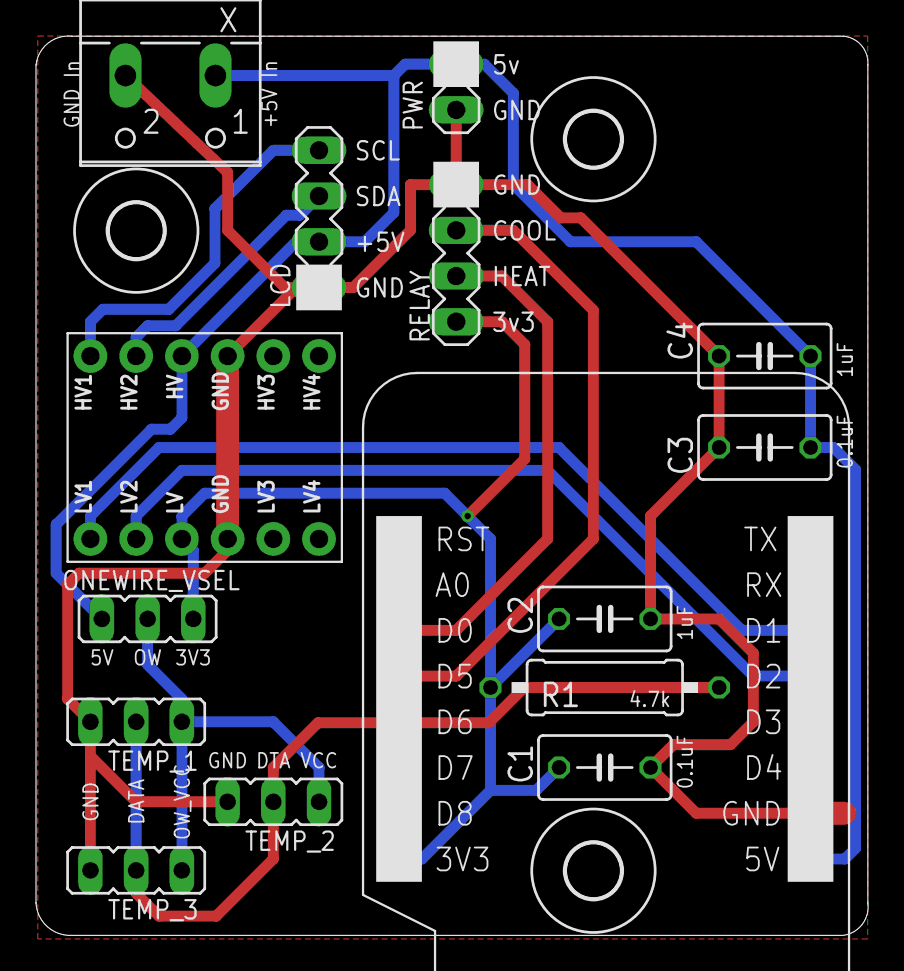
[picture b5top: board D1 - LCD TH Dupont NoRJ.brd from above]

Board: 2 copper layers, 46.2 x 50.0 mm, 18 parts (0 on the bottom side), 11 nets.

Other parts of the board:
U$2, U$4, U$5: 3,0

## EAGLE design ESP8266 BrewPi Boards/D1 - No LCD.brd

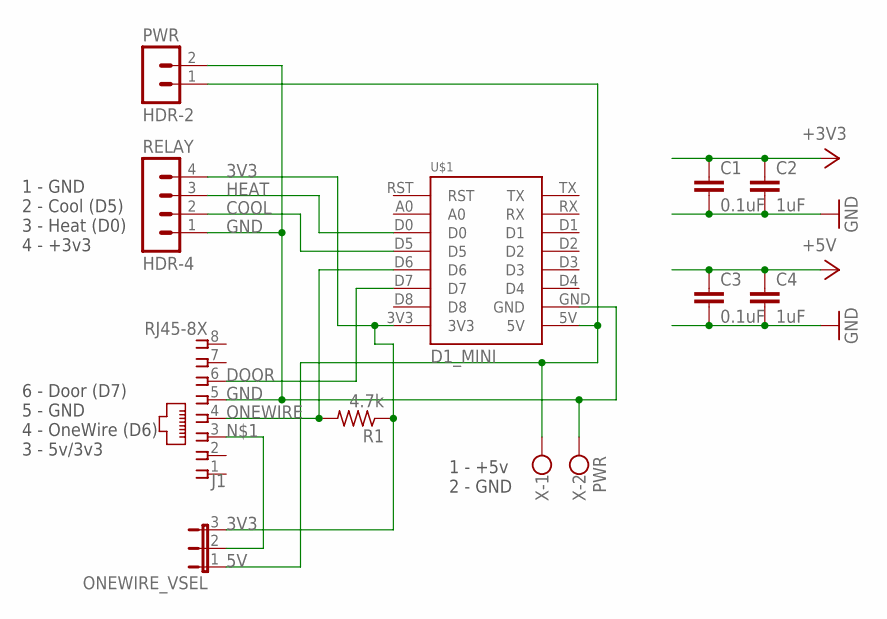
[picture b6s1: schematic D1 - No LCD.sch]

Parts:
C1, C3: 0.1uF; C050-030X075
C2, C4: 1uF; C050-030X075
J1: RJ45-8X; RJ45-NS-XDIM
ONEWIRE_VSEL: JP2ENOLABEL; JP2-NOLABEL
PWR: HDR-2; HDR-2_VERT
R1: 4.7k; 0309/12
RELAY: HDR-4; HDR-4_VERT
U$1: D1_MINI; WEMOS-CLEAN
X: PWR; W237-102

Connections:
3V3: C1.1, C2.1, ONEWIRE_VSEL.3, R1.1, RELAY.4, U$1.3V3
5V: C3.1, C4.1, ONEWIRE_VSEL.1, PWR.1, U$1.5V, X.1
COOL: RELAY.2, U$1.D5
DOOR: J1.6, U$1.D7
GND: C1.2, C2.2, C3.2, C4.2, J1.5, PWR.2, RELAY.1, U$1.GND, X.2
HEAT: RELAY.3, U$1.D0
unnamed: J1.3, ONEWIRE_VSEL.2
ONEWIRE: J1.4, R1.2, U$1.D6

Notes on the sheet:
1 - GND 2 - Cool (D5) 3 - Heat (D0) 4 - +3v3
6 - Door (D7) 5 - GND 4 - OneWire (D6) 3 - 5v/3v3
1 - +5v 2 - GND

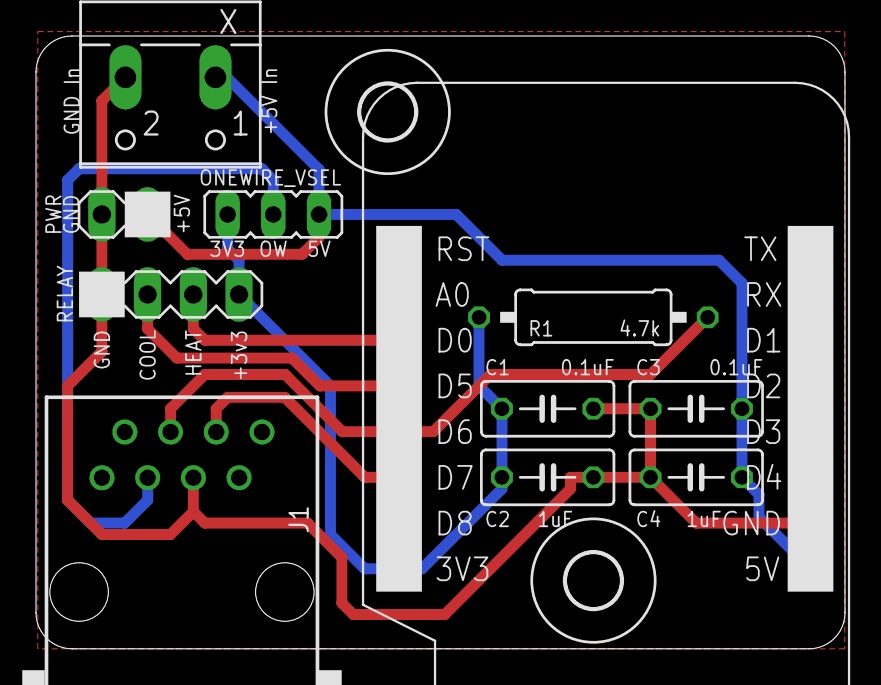
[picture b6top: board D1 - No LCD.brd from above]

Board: 2 copper layers, 44.9 x 34.0 mm, 13 parts (0 on the bottom side), 8 nets.

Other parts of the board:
U$4, U$5: 3,0

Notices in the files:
parts and their libraries:
SparkFun-Boards: Licensing: Creative Commons ShareAlike 4.0 International - https://creativecommons.org/licenses/by-sa/4.0
COPYRIGHT: Copyright (C) 2024 Ultra Librarian. All rights reserved.
